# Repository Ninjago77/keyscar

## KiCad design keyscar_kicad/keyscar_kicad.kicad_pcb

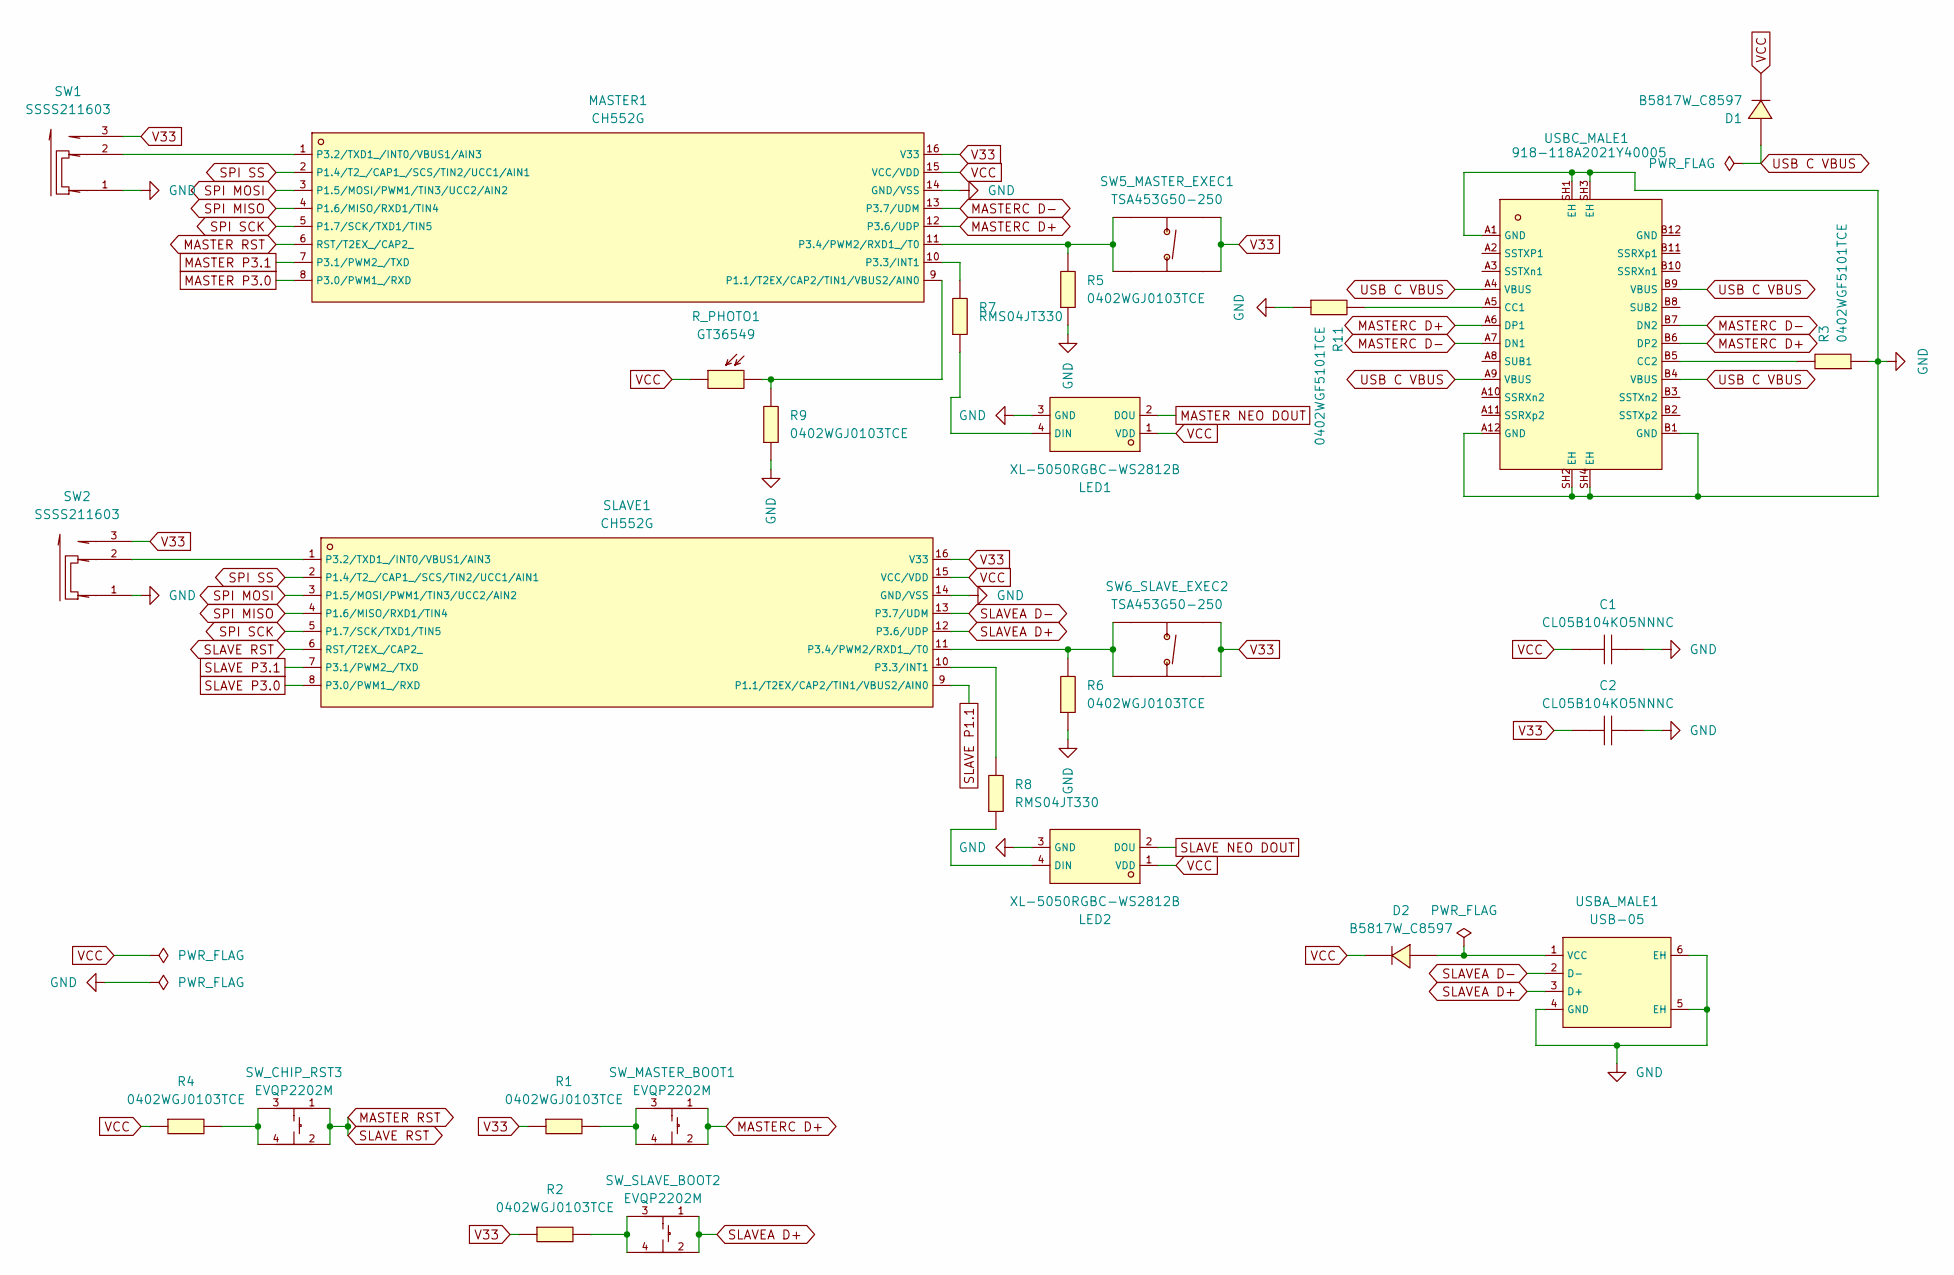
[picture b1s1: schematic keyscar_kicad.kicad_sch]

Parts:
C1, C2: CL05B104KO5NNNC; C0402; LCSC C1525
D1, D2: B5817W_C8597; SOD-123_L2.8-W1.8-LS3.7-RD; LCSC C8597
LED1, LED2: XL-5050RGBC-WS2812B; LED-SMD_4P-L5.0-W5.0-BL_XL-5050RGBC; LCSC C2843785
MASTER1: CH552G; SOP-16_L10.0-W3.9-P1.27-LS6.0-BL; LCSC C111292
R1, R2, R4, R5, R6, R9: 0402WGJ0103TCE; R0402; LCSC C25531
R3, R11: 0402WGF5101TCE; R0402; LCSC C25905
R7, R8: RMS04JT330; R0402; LCSC C208984
R_PHOTO1: GT36549; RES-SMD_L3.6-W2.4; LCSC C2904883
SLAVE1: CH552G; SOP-16_L10.0-W3.9-P1.27-LS6.0-BL; LCSC C111292
SW1, SW2: SSSS211603; SW-SMD_SSSS211603; LCSC C125040
SW5_MASTER_EXEC1, SW6_SLAVE_EXEC2: TSA453G50-250; KEY-SMD_4P-L4.5-W4.5-P3.00-LS7.5; LCSC C294495
SW_CHIP_RST3: EVQP2202M; SW-SMD_L4.7-W3.5-P2.00-LS5.2_EVQP2202M; LCSC C528967
SW_MASTER_BOOT1: EVQP2202M; SW-SMD_L4.7-W3.5-P2.00-LS5.2_EVQP2202M; LCSC C528967
SW_SLAVE_BOOT2: EVQP2202M; SW-SMD_L4.7-W3.5-P2.00-LS5.2_EVQP2202M; LCSC C528967
USBA_MALE1: USB-05; USB-A-TH_USB-05; LCSC C112454
USBC_MALE1: 918-118A2021Y40005; USB-C-SMD_918-118A2021Y40005; LCSC C2763098

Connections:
GND: C1.2, C2.2, LED1.3 (GND), LED2.3 (GND), MASTER1.14 (GND/VSS), R3.1, R5.1, R6.1, R9.1, R11.1, SLAVE1.14 (GND/VSS), SW1.1, SW2.1, USBA_MALE1.4 (GND), USBA_MALE1.5 (EH), USBA_MALE1.6 (EH), USBC_MALE1.A1 (GND), USBC_MALE1.A12 (GND), USBC_MALE1.B1 (GND), USBC_MALE1.SH1 (EH), USBC_MALE1.SH2 (EH), USBC_MALE1.SH3 (EH), USBC_MALE1.SH4 (EH)
MASTER NEO DOUT: LED1.2 (DOU)
MASTER P3.0: MASTER1.8 (P3.0/PWM1_/RXD)
MASTER P3.1: MASTER1.7 (P3.1/PWM2_/TXD)
MASTER RST: MASTER1.6 (RST/T2EX_/CAP2_), SLAVE1.6 (RST/T2EX_/CAP2_), SW_CHIP_RST3.1, SW_CHIP_RST3.2
MASTERC D+: MASTER1.12 (P3.6/UDP), SW_MASTER_BOOT1.1, SW_MASTER_BOOT1.2, USBC_MALE1.A6 (DP1), USBC_MALE1.B6 (DP2)
MASTERC D-: MASTER1.13 (P3.7/UDM), USBC_MALE1.A7 (DN1), USBC_MALE1.B7 (DN2)
unnamed: D2.2 (A), USBA_MALE1.1 (VCC)
unnamed: LED1.4 (DIN), R7.1
unnamed: LED2.4 (DIN), R8.1
unnamed: MASTER1.9 (P1.1/T2EX/CAP2/TIN1/VBUS2/AIN0), R9.2, R_PHOTO1.2
unnamed: MASTER1.1 (P3.2/TXD1_/INT0/VBUS1/AIN3), SW1.2
unnamed: MASTER1.10 (P3.3/INT1), R7.2
unnamed: MASTER1.11 (P3.4/PWM2/RXD1_/T0), R5.2, SW5_MASTER_EXEC1.2, SW5_MASTER_EXEC1.4
unnamed: R1.2, SW_MASTER_BOOT1.3, SW_MASTER_BOOT1.4
unnamed: R2.2, SW_SLAVE_BOOT2.3, SW_SLAVE_BOOT2.4
unnamed: R4.2, SW_CHIP_RST3.3, SW_CHIP_RST3.4
unnamed: SLAVE1.1 (P3.2/TXD1_/INT0/VBUS1/AIN3), SW2.2
unnamed: R8.2, SLAVE1.10 (P3.3/INT1)
unnamed: R6.2, SLAVE1.11 (P3.4/PWM2/RXD1_/T0), SW6_SLAVE_EXEC2.2, SW6_SLAVE_EXEC2.4
unnamed: R11.2, USBC_MALE1.A5 (CC1)
unnamed: R3.2, USBC_MALE1.B5 (CC2)
SLAVE NEO DOUT: LED2.2 (DOU)
SLAVE P1.1: SLAVE1.9 (P1.1/T2EX/CAP2/TIN1/VBUS2/AIN0)
SLAVE P3.0: SLAVE1.8 (P3.0/PWM1_/RXD)
SLAVE P3.1: SLAVE1.7 (P3.1/PWM2_/TXD)
SLAVEA D+: SLAVE1.12 (P3.6/UDP), SW_SLAVE_BOOT2.1, SW_SLAVE_BOOT2.2, USBA_MALE1.3 (D+)
SLAVEA D-: SLAVE1.13 (P3.7/UDM), USBA_MALE1.2 (D-)
SPI MISO: MASTER1.4 (P1.6/MISO/RXD1/TIN4), SLAVE1.4 (P1.6/MISO/RXD1/TIN4)
SPI MOSI: MASTER1.3 (P1.5/MOSI/PWM1/TIN3/UCC2/AIN2), SLAVE1.3 (P1.5/MOSI/PWM1/TIN3/UCC2/AIN2)
SPI SCK: MASTER1.5 (P1.7/SCK/TXD1/TIN5), SLAVE1.5 (P1.7/SCK/TXD1/TIN5)
SPI SS: MASTER1.2 (P1.4/T2_/CAP1_/SCS/TIN2/UCC1/AIN1), SLAVE1.2 (P1.4/T2_/CAP1_/SCS/TIN2/UCC1/AIN1)
USB C VBUS: D1.2 (A), USBC_MALE1.A4 (VBUS), USBC_MALE1.A9 (VBUS), USBC_MALE1.B4 (VBUS), USBC_MALE1.B9 (VBUS)
V33: C2.1, MASTER1.16 (V33), R1.1, R2.1, SLAVE1.16 (V33), SW1.3, SW2.3, SW5_MASTER_EXEC1.1, SW5_MASTER_EXEC1.3, SW6_SLAVE_EXEC2.1, SW6_SLAVE_EXEC2.3
VCC: C1.1, D1.1 (C), D2.1 (C), LED1.1 (VDD), LED2.1 (VDD), MASTER1.15 (VCC/VDD), R4.1, R_PHOTO1.1, SLAVE1.15 (VCC/VDD)

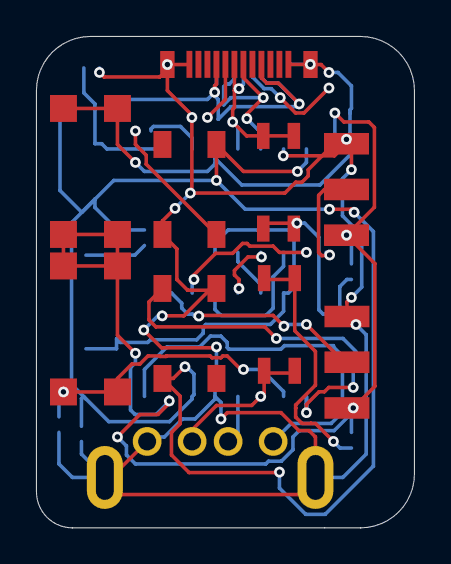
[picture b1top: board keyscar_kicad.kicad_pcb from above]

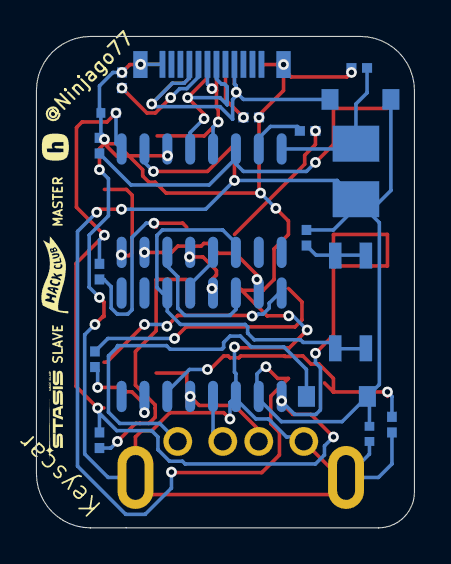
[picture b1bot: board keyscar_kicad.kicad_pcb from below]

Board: 2 copper layers, 21.0 x 27.3 mm, 28 parts (18 on the bottom side), 28 nets.

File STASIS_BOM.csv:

NAME,PURPOSE,QUANTITY,TOTAL COST (USD),LINK,DISTRIBUTOR
CL05B104KO5NNNC (100nF Capacitor),Capacitor,20,0.026,https://jlcpcb.com/partdetail/C1525,JLCPCB
B5817W,Diode,14,0.5852,https://jlcpcb.com/partdetail/C8597,JLCPCB
XL-5050RGBC-2812B,RGB LED,14,0.7504,https://jlcpcb.com/partdetail/C2843785,JLCPCB
0402WGJ0103TCE (10k Resistor),Resistor,42,0.0294,https://jlcpcb.com/partdetail/C25531,JLCPCB
RMS04JT330 (33 ohm Resistor),Resistor,20,0.032,https://jlcpcb.com/partdetail/C208984,JLCPCB
0402WGF5101TCE (5.1k Resistor),Resistor,20,0.016,https://jlcpcb.com/partdetail/C25905,JLCPCB
GT36549,Photoresistor / Sensor,5,0.9415,https://jlcpcb.com/partdetail/C2904883,JLCPCB
CH552G,Microcontroller,10,4.616,https://jlcpcb.com/partdetail/C111292,JLCPCB
SSSS211603,Slide Switch,10,3.889,https://jlcpcb.com/partdetail/C125040,JLCPCB
TSA453G50-250,Tactile Switch,15,0.435,https://jlcpcb.com/partdetail/C294495,JLCPCB
EVQP2202M,Tactile Switch,15,4.6245,https://jlcpcb.com/partdetail/C528967,JLCPCB
USB-05,USB-A Male Connector,5,0.3885,https://jlcpcb.com/partdetail/C112454,JLCPCB
918-118A2021Y40005,USB-C Male Connector,5,2.221,https://jlcpcb.com/partdetail/C2763098,JLCPCB
PCB: Special Offer,PCB Manufacturing,1,4,https://jlcpcb.com,JLCPCB
Standard PCBA: Setup Fee,PCB Assembly,1,50.74,https://cart.jlcpcb.com/smt-order,JLCPCB
Standard PCBA: Stencil,PCB Assembly,1,16.3,https://cart.jlcpcb.com/smt-order,JLCPCB
Standard PCBA: Feeders Loading fee,PCB Assembly,1,18.24,https://cart.jlcpcb.com/smt-order,JLCPCB
Standard PCBA: SMT Assembly,PCB Assembly,1,1.2,https://cart.jlcpcb.com/smt-order,JLCPCB
Standard PCBA: Hand-soldering labor fee,PCB Assembly,1,3.55,https://cart.jlcpcb.com/smt-order,JLCPCB
Standard PCBA: Manual Assembly,PCB Assembly,1,0.49,https://cart.jlcpcb.com/smt-order,JLCPCB
Standard PCBA: PCB assembly fixture,PCB Assembly,1,16.3,https://cart.jlcpcb.com/smt-order,JLCPCB
Standard PCBA: Packaging fee,PCB Assembly,1,0.49,https://cart.jlcpcb.com/smt-order,JLCPCB

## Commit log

2026-03-17 added journal 2
2026-03-18 rearrange
2026-03-18 actually did some research hoarding and schematic making
2026-03-18 Add GNU General Public License v3
2026-03-19 pre-jclpcb components safety commit
2026-03-19 Fixing Schematic, Redoing it with Part-Symbols & Connecting footprints, symbols, 3d models alltogether
2026-03-20 Getting Started on Wiring the PCB & Substituting Parts
2026-03-20 Wrapping up the PCB, wiring the VCC, V33, GND
2026-03-20 medium commit
2026-03-20 safety commit
2026-03-21 yippee
2026-03-21 Wrapped up PCB & Silkscreen, worked on BOM & Purchasing
2026-03-21 safety commit again
2026-03-21 :( Old peak 2 sided
2026-03-21 Working on Silkscreen & Suffering through the Pain that is PCBA ordering
2026-03-22 Worked on converting BOM to Stasis BOM
